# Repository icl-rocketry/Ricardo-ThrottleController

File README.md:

# C.H.A.D - Servo Control Board
2 servo channels controlled by PWM, with a buck converter set to output 6V or 8.4V @ 12A depending on configuration.

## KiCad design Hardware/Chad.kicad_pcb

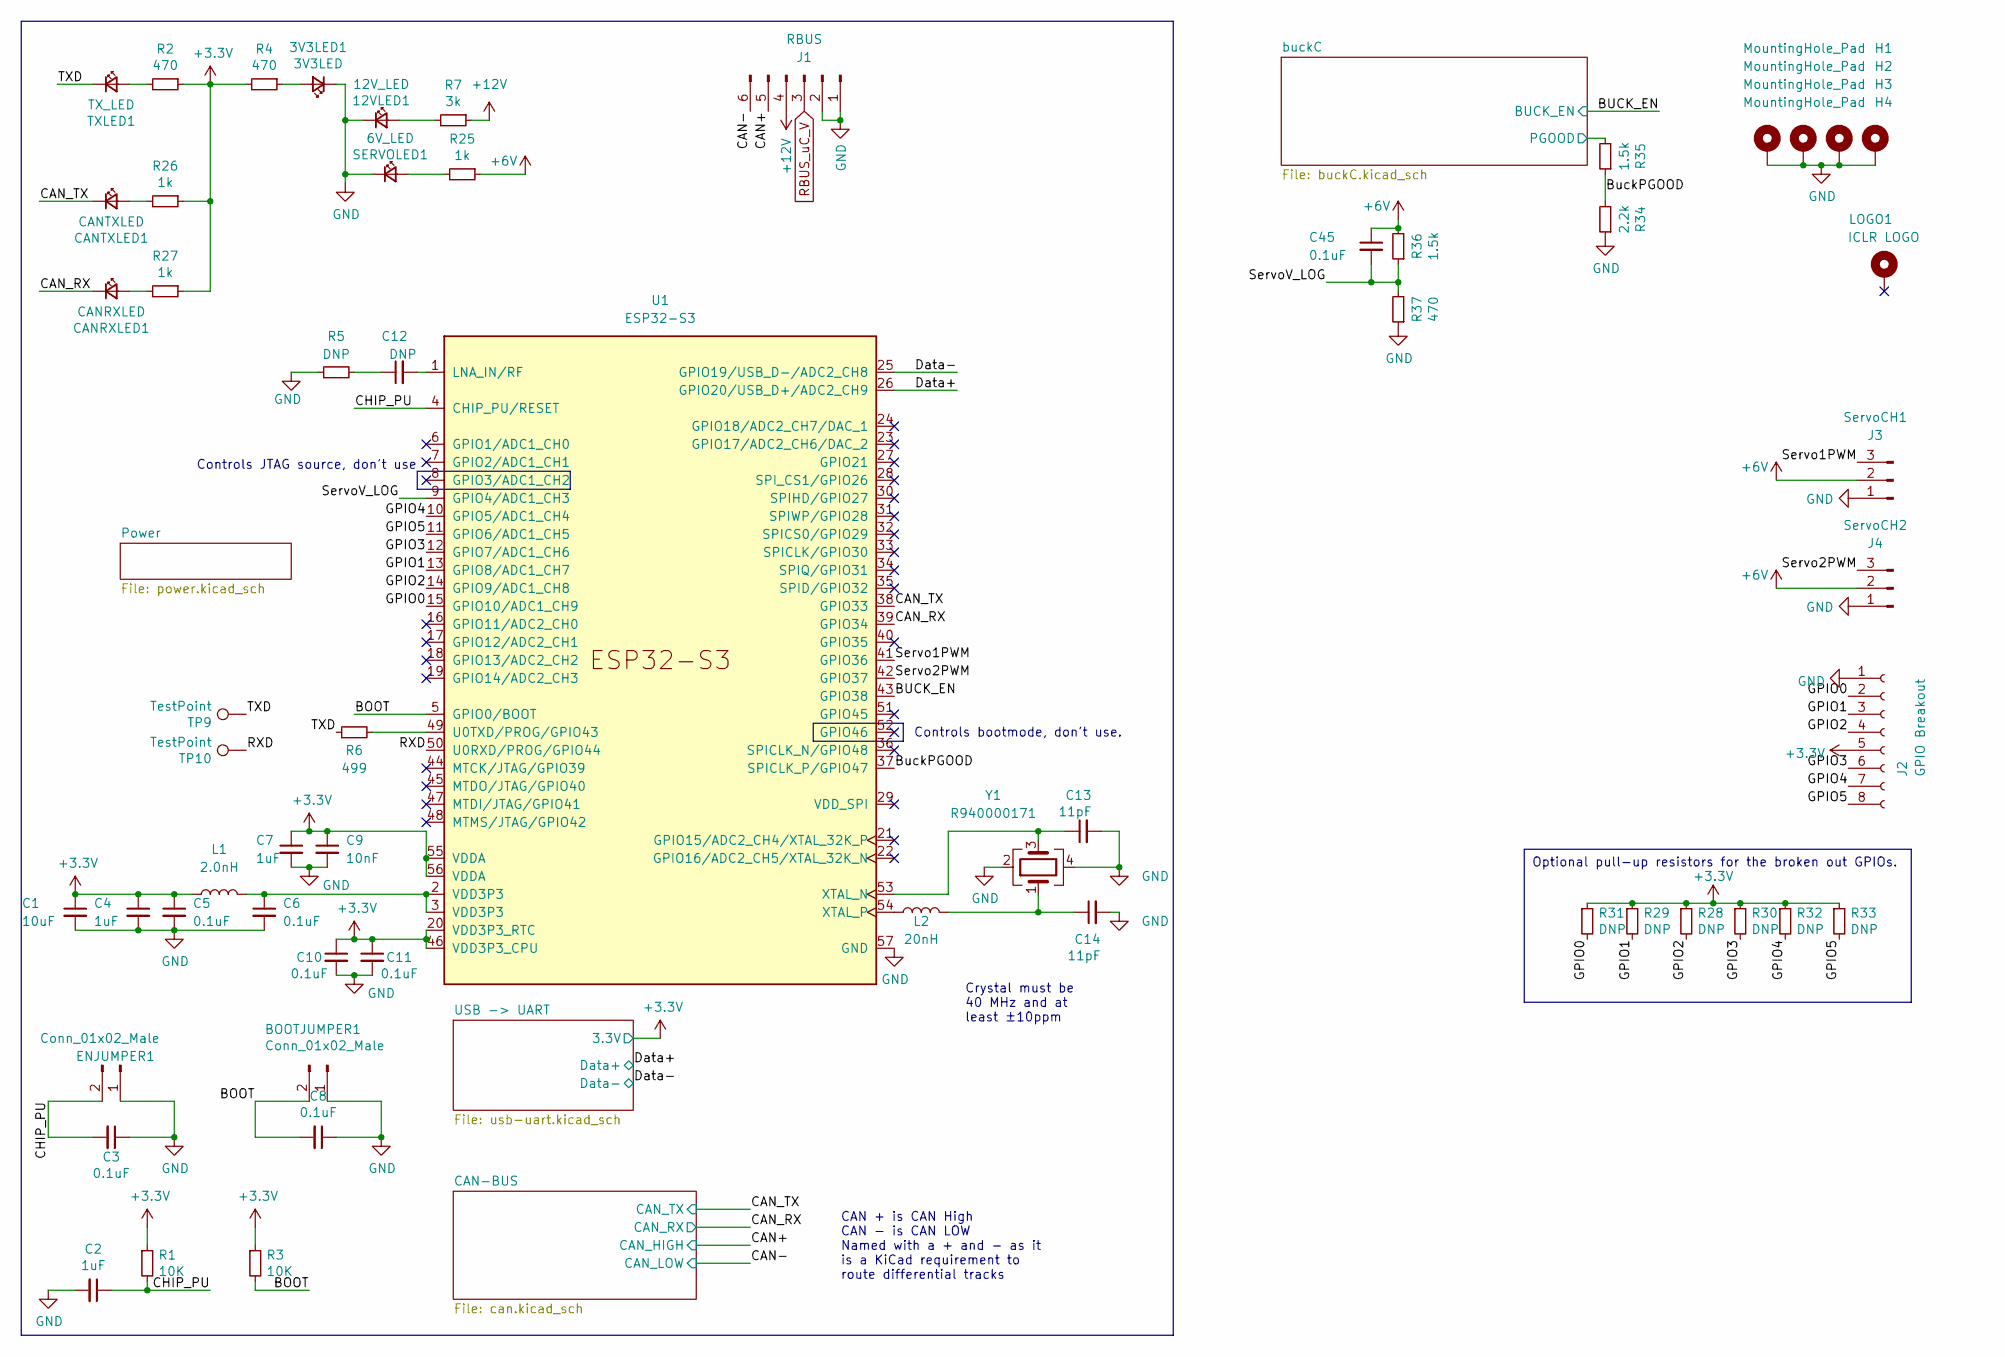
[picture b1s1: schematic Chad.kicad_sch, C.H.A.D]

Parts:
3V3LED1: 3V3LED; LED_0402_1005Metric
12VLED1: 12V_LED; LED_0402_1005Metric
BOOTJUMPER1: Conn_01x02_Male; PinHeader_1x02_P2.54mm_Vertical
C1: 10uF; C_0402_1005Metric
C2, C4, C7: 1uF; C_0402_1005Metric
C3, C5, C6, C8, C10, C11, C45: 0.1uF; C_0402_1005Metric
C9: 10nF; C_0402_1005Metric
C12: DNP; C_0402_1005Metric
C13, C14: 11pF; C_0402_1005Metric
CANRXLED1: CANRXLED; LED_0402_1005Metric
CANTXLED1: CANTXLED; LED_0402_1005Metric
ENJUMPER1: Conn_01x02_Male; PinHeader_1x02_P2.54mm_Vertical
H1, H2, H3, H4: MountingHole_Pad; MountingHole_3.2mm_M3_DIN965_Pad
J1: RBUS; Molex_Mini-Fit_Jr_5569-06A2_2x03_P4.20mm_Horizontal
J2: GPIO Breakout; PinSocket_2x04_P2.54mm_Vertical
J3: ServoCH1; Molex_Nano-Fit_105313-xx03_1x03_P2.50mm_Horizontal
J4: ServoCH2; Molex_Nano-Fit_105313-xx03_1x03_P2.50mm_Horizontal
L1: 2.0nH; L_0402_1005Metric
L2: 20nH; L_0402_1005Metric
LOGO1: ICLR LOGO; iclr_logo_estd2018_10mm
R1, R3: 10K; R_0402_1005Metric
R2, R4, R37: 470; R_0402_1005Metric
R5, R28, R29, R30, R31, R32, R33: DNP; R_0402_1005Metric
R6: 499; R_0402_1005Metric
R7: 3k; R_0402_1005Metric
R25, R26, R27: 1k; R_0402_1005Metric
R34: 2.2k; R_0402_1005Metric
R35, R36: 1.5k; R_0402_1005Metric
SERVOLED1: 6V_LED; LED_0402_1005Metric
TP9, TP10: TestPoint; TestPoint_Pad_D1.0mm
TXLED1: TX_LED; LED_0402_1005Metric
U1: ESP32-S3; QFN40P700X700X90-57N
Y1: R940000171; Crystal_SMD_2016-4Pin_2.0x1.6mm

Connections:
+3V3: C1.1, C4.1, C5.1, C7.1, C9.1, C10.1, C11.1, J2.5, L1.1, R1.1, R2.1, R3.1, R4.2, R26.1, R27.1, R28.1, R29.1, R30.1, R31.1, R32.1, R33.1, U1.20 (VDD3P3_RTC), U1.46 (VDD3P3_CPU), U1.55 (VDDA), U1.56 (VDDA); also elsewhere on the board
+6V: C45.1, J3.2, J4.2, R25.1, R36.2; also elsewhere on the board
+12V: J1.4, R7.1; also elsewhere on the board
/BOOT: BOOTJUMPER1.2, C8.2, R3.2, U1.5 (GPIO0/BOOT)
/BUCK_EN: U1.43 (GPIO38); also elsewhere on the board
/BuckPGOOD: R34.2, R35.1, U1.37 (SPICLK_P/GPIO47)
/CAN+: J1.5; also elsewhere on the board
/CAN-: J1.6; also elsewhere on the board
/CAN_RX: CANRXLED1.1 (K), U1.39 (GPIO34); also elsewhere on the board
/CAN_TX: CANTXLED1.1 (K), U1.38 (GPIO33); also elsewhere on the board
/CHIP_PU: C2.1, C3.2, ENJUMPER1.2, R1.2, U1.4 (CHIP_PU/RESET)
/Data+: U1.26 (GPIO20/USB_D+/ADC2_CH9); also elsewhere on the board
/Data-: U1.25 (GPIO19/USB_D-/ADC2_CH8); also elsewhere on the board
/GPIO0: J2.2, R31.2, U1.15 (GPIO10/ADC1_CH9)
/GPIO1: J2.3, R29.2, U1.13 (GPIO8/ADC1_CH7)
/GPIO2: J2.4, R28.2, U1.14 (GPIO9/ADC1_CH8)
/GPIO3: J2.6, R30.2, U1.12 (GPIO7/ADC1_CH6)
/GPIO4: J2.7, R32.2, U1.10 (GPIO5/ADC1_CH4)
/GPIO5: J2.8, R33.2, U1.11 (GPIO6/ADC1_CH5)
/RXD: TP10.1, U1.50 (U0RXD/PROG/GPIO44)
/Servo1PWM: J3.3, U1.41 (GPIO36)
/Servo2PWM: J4.3, U1.42 (GPIO37)
/ServoV_LOG: C45.2, R36.1, R37.2, U1.9 (GPIO4/ADC1_CH3)
/TXD: R6.1, TP9.1, TXLED1.1 (K)
/buckC/PGOOD: R35.2; also elsewhere on the board
GND: 3V3LED1.1 (K), 12VLED1.1 (K), BOOTJUMPER1.1, C1.2, C2.2, C3.1, C4.2, C5.2, C6.2, C7.2, C8.1, C9.2, C10.2, C11.2, C13.2, C14.2, ENJUMPER1.1, H1.1, H2.1, H3.1, H4.1, J1.1, J1.2, J2.1, J3.1, J4.1, R5.1, R34.1, R37.1, SERVOLED1.1 (K), U1.57 (GND), Y1.2, Y1.4; also elsewhere on the board
unnamed: 3V3LED1.2 (A), R4.1
unnamed: 12VLED1.2 (A), R7.2
unnamed: C6.1, L1.2, U1.2 (VDD3P3), U1.3 (VDD3P3)
unnamed: C12.1, R5.2
unnamed: C14.1, L2.2, Y1.1
unnamed: CANRXLED1.2 (A), R27.2
unnamed: CANTXLED1.2 (A), R26.2
unnamed: R25.2, SERVOLED1.2 (A)
unnamed: R2.2, TXLED1.2 (A)
unnamed: C12.2, U1.1 (LNA_IN/RF)
unnamed: R6.2, U1.49 (U0TXD/PROG/GPIO43)
unnamed: C13.1, U1.53 (XTAL_N), Y1.3
unnamed: L2.1, U1.54 (XTAL_P)
RBUS_uC_V: J1.3; also elsewhere on the board

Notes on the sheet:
Crystal must be 40 MHz and at least ±10ppm
Optional pull-up resistors for the broken out GPIOs.
Controls bootmode, don't use.
CAN + is CAN High CAN - is CAN LOW Named with a + and - as it is a KiCad requirement to route differential tracks
Controls JTAG source, don't use

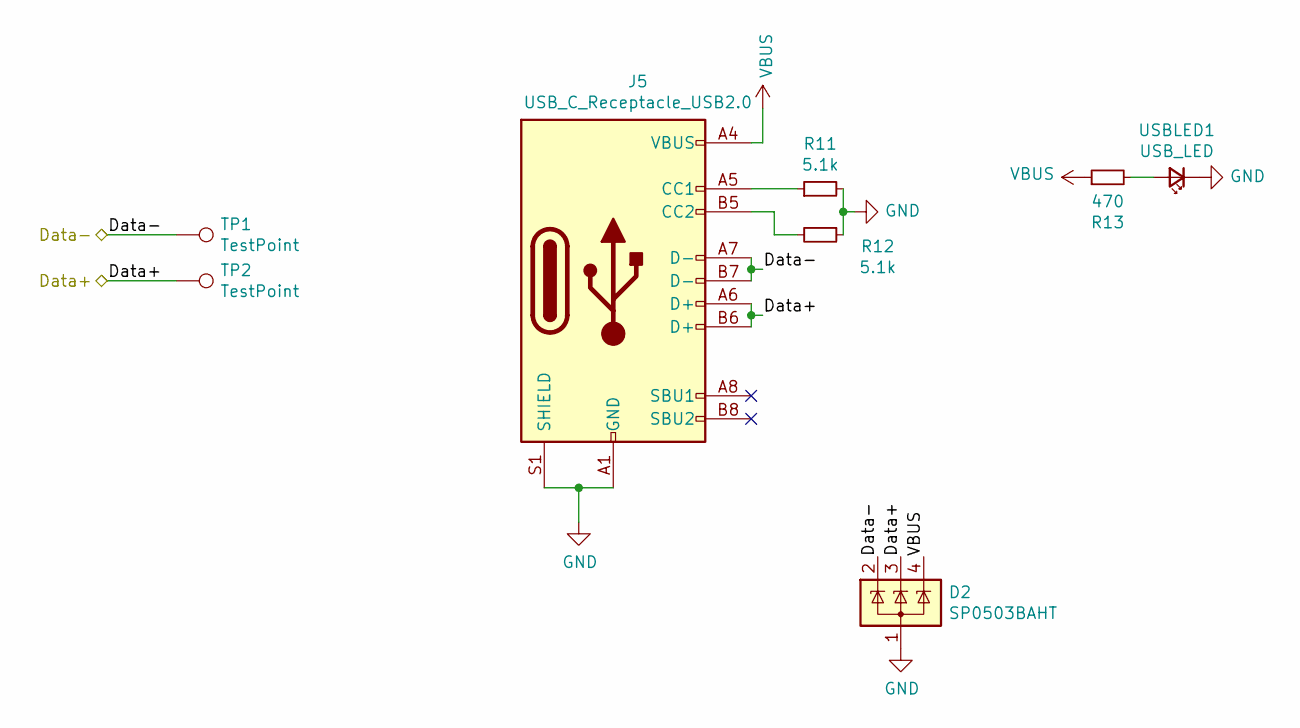
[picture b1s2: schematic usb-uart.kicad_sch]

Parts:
D2: SP0503BAHT; SOT-143
J5: USB_C_Receptacle_USB2.0; USB_C_Receptacle_Palconn_UTC16-G
R11, R12: 5.1k; R_0402_1005Metric
R13: 470; R_0402_1005Metric
TP1, TP2: TestPoint; TestPoint_Pad_D1.0mm
USBLED1: USB_LED; LED_0402_1005Metric

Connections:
/Data+: D2.3 (K), J5.A6 (D+), J5.B6 (D+), TP2.1; also elsewhere on the board
/Data-: D2.2 (K), J5.A7 (D-), J5.B7 (D-), TP1.1; also elsewhere on the board
GND: D2.1 (A), J5.A1 (GND), J5.A12 (GND), J5.B1 (GND), J5.B12 (GND), J5.S1 (SHIELD), R11.2, R12.1, USBLED1.1 (K); also elsewhere on the board
unnamed: J5.A5 (CC1), R11.1
unnamed: J5.B5 (CC2), R12.2
unnamed: R13.2, USBLED1.2 (A)
VBUS: D2.4 (K), J5.A4 (VBUS), J5.A9 (VBUS), J5.B4 (VBUS), J5.B9 (VBUS), R13.1; also elsewhere on the board

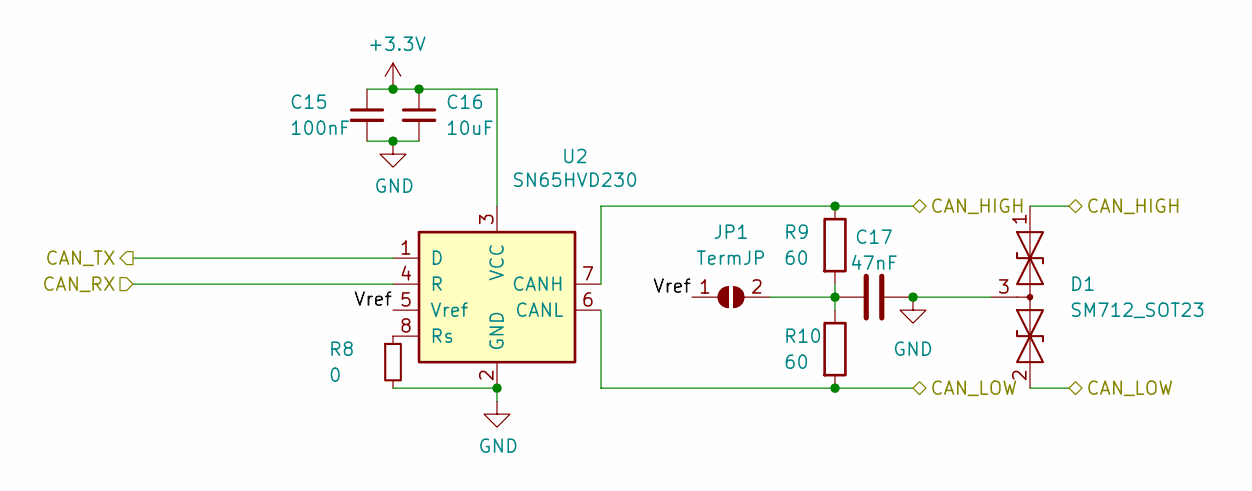
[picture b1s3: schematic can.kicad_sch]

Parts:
C15: 100nF; C_0402_1005Metric
C16: 10uF; C_0402_1005Metric
C17: 47nF; C_0402_1005Metric
D1: SM712_SOT23; SOT-23
JP1: TermJP; SmallerSolderJP
R8: 0; R_0603_1608Metric
R9, R10: 60; R_0603_1608Metric
U2: SN65HVD230; SOIC-8_3.9x4.9mm_P1.27mm

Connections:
+3V3: C15.1, C16.1, U2.3 (VCC); also elsewhere on the board
/CAN+: D1.1 (A1), R9.1, U2.7 (CANH); also elsewhere on the board
/CAN-: D1.2 (A2), R10.2, U2.6 (CANL); also elsewhere on the board
/CAN-BUS/Vref: JP1.1 (A), U2.5 (Vref)
/CAN_RX: U2.4 (R); also elsewhere on the board
/CAN_TX: U2.1 (D); also elsewhere on the board
GND: C15.2, C16.2, C17.2, D1.3 (common), R8.2, U2.2 (GND); also elsewhere on the board
unnamed: C17.1, JP1.2 (B), R9.2, R10.1
unnamed: R8.1, U2.8 (Rs)

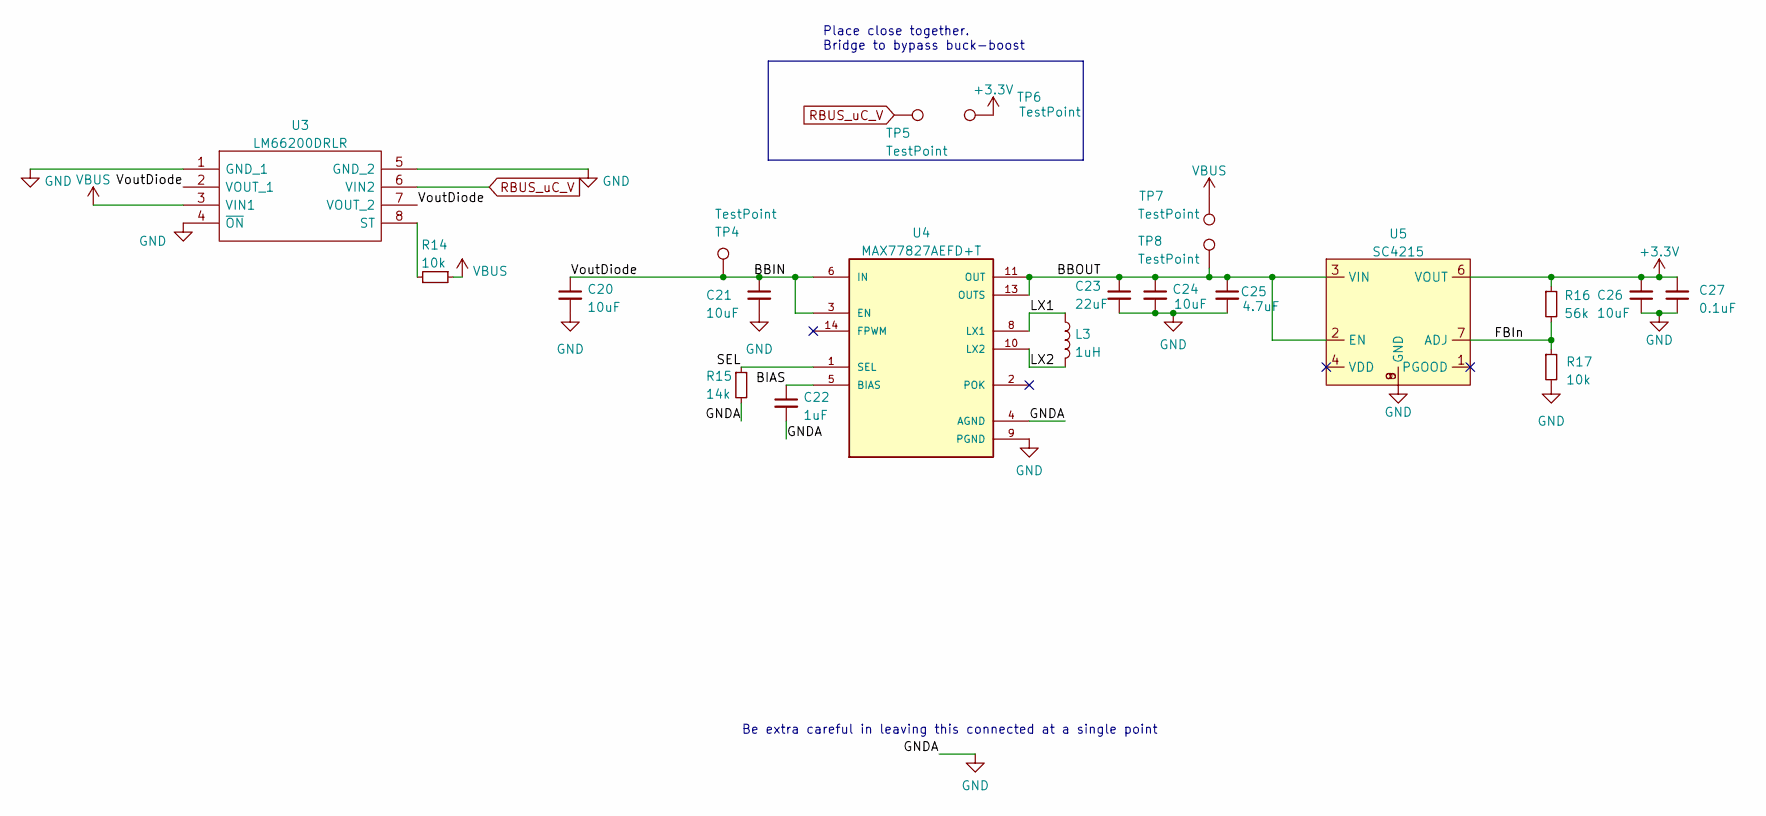
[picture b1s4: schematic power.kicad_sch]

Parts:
C20, C24, C26: 10uF; C_0402_1005Metric
C21: 10uF; C_0603_1608Metric
C22: 1uF; C_0402_1005Metric
C23: 22uF; C_0603_1608Metric
C25: 4.7uF; C_0402_1005Metric
C27: 0.1uF; C_0402_1005Metric
L3: 1uH; L_0805_2012Metric
R14, R17: 10k; R_0402_1005Metric
R15: 14k; R_0402_1005Metric
R16: 56k; R_0402_1005Metric
TP4, TP5, TP6, TP7, TP8: TestPoint; TestPoint_Pad_D1.5mm
U3: LM66200DRLR; SOTFL50P160X60-8N; Manufacturer_Part_Number LM66200DRLR; Mouser Part Number 595-LM66200DRLR
U4: MAX77827AEFD+T; CONV_MAX77827AEFD+T; PARTREV B
U5: SC4215; SOIC127P599X175-9N

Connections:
+3V3: C26.2, C27.2, R16.1, TP6.1, U5.6 (VOUT); also elsewhere on the board
/Power/BBIN: C20.1, C21.1, TP4.1, U3.2 (VOUT_1), U3.7 (VOUT_2), U4.3 (EN), U4.6 (IN)
/Power/BBOUT: C23.1, C24.1, C25.1, TP8.1, U4.11 (OUT), U4.13 (OUTS), U5.2 (EN), U5.3 (VIN)
/Power/BIAS: C22.1, U4.5 (BIAS)
/Power/FBIn: R16.2, R17.1, U5.7 (ADJ)
/Power/LX1: L3.1, U4.8 (LX1)
/Power/LX2: L3.2, U4.10 (LX2)
/Power/SEL: R15.1, U4.1 (SEL)
GND: C20.2, C21.2, C22.2, C23.2, C24.2, C25.2, C26.1, C27.1, R15.2, R17.2, U3.1 (GND_1), U3.4 (~ON), U3.5 (GND_2), U4.4 (AGND), U4.9 (PGND), U5.8 (GND), U5.9 (GND); also elsewhere on the board
unnamed: R14.2, U3.8 (ST)
RBUS_uC_V: TP5.1, U3.6 (VIN2); also elsewhere on the board
VBUS: R14.1, TP7.1, U3.3 (VIN1); also elsewhere on the board

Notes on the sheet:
Place close together. Bridge to bypass buck-boost
Be extra careful in leaving this connected at a single point

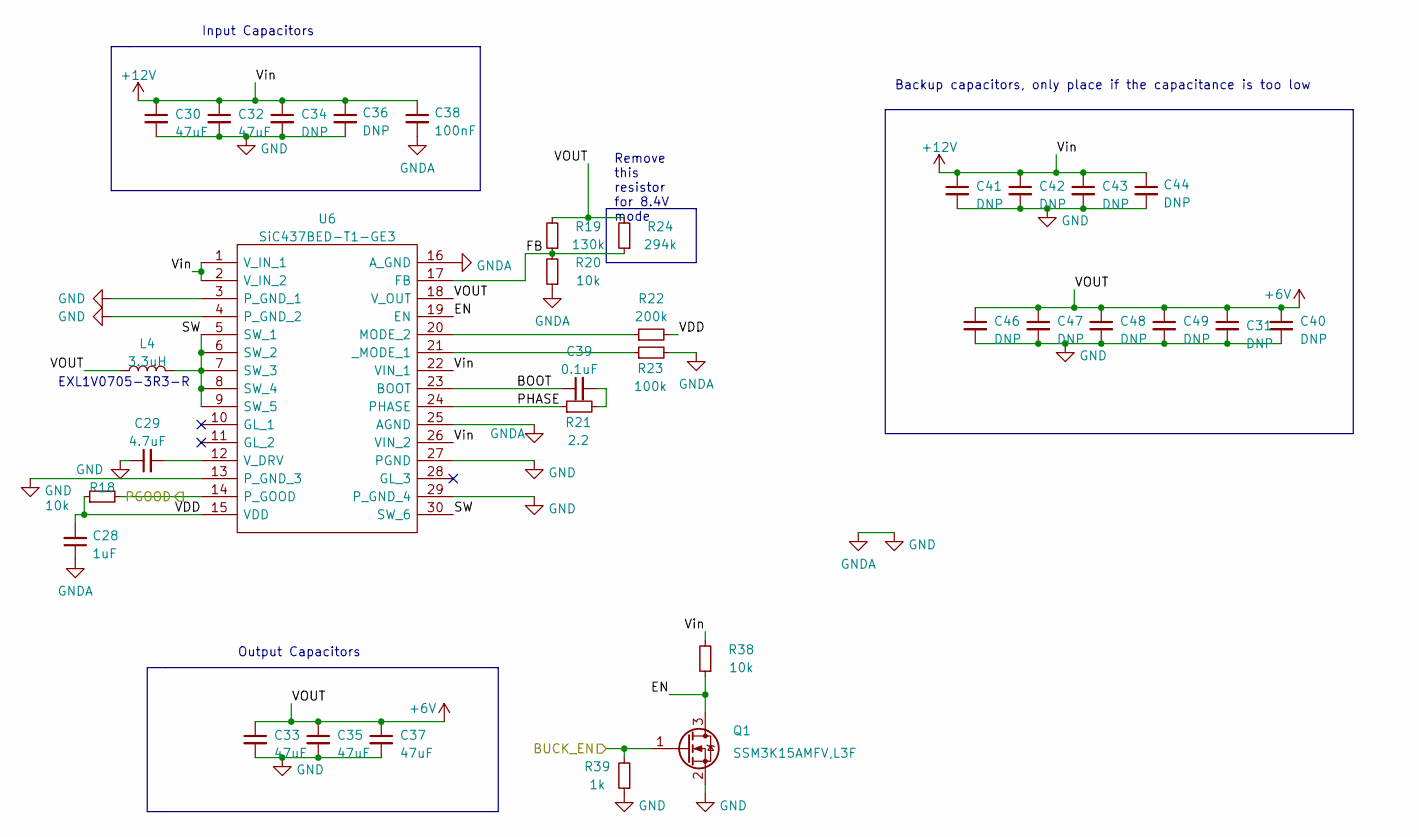
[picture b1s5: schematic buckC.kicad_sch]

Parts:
C28: 1uF; C_0402_1005Metric
C29: 4.7uF; C_0402_1005Metric
C30, C32, C33, C35, C37: 47uF; C_1206_3216Metric
C31, C34, C36, C40, C41, C42, C43, C44, C47, C49: DNP; C_1206_3216Metric
C38: 100nF; C_0402_1005Metric
C39: 0.1uF; C_0402_1005Metric
C46, C48: DNP; C_0805_2012Metric
L4: 3.3uH; EXL1V07053R3R
Q1: SSM3K15AMFV,L3F; SOT-723
R18, R20, R38: 10k; R_0402_1005Metric
R19: 130k; R_0402_1005Metric
R21: 2.2; R_0402_1005Metric
R22: 200k; R_0402_1005Metric
R23: 100k; R_0402_1005Metric
R24: 294k; R_0402_1005Metric
R39: 1k; R_0402_1005Metric
U6: SiC437BED-T1-GE3; SiC437BEDT1GE3; Manufacturer_Part_Number SiC437BED-T1-GE3; Mouser Part Number 78-SIC437BED-T1-GE3

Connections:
+6V: C31.1, C33.1, C35.1, C37.1, C40.1, C46.1, C47.1, C48.1, C49.1, L4.1, R19.2, R24.2, U6.18 (V_OUT); also elsewhere on the board
+12V: C30.1, C32.1, C34.1, C36.1, C38.1, C41.1, C42.1, C43.1, C44.1, R38.2, U6.1 (V_IN_1), U6.2 (V_IN_2), U6.22 (VIN_1), U6.26 (VIN_2); also elsewhere on the board
/BUCK_EN: Q1.1 (G), R39.2; also elsewhere on the board
/buckC/BOOT: C39.1, U6.23 (BOOT)
/buckC/EN: Q1.3 (D), R38.1, U6.19 (EN)
/buckC/FB: R19.1, R20.2, R24.1, U6.17 (FB)
/buckC/PGOOD: R18.2, U6.14 (P_GOOD); also elsewhere on the board
/buckC/PHASE: R21.1, U6.24 (PHASE)
/buckC/SW: L4.2, U6.5 (SW_1), U6.6 (SW_2), U6.7 (SW_3), U6.8 (SW_4), U6.9 (SW_5), U6.30 (SW_6)
/buckC/VDD: C28.2, R18.1, R22.2, U6.15 (VDD)
GND: C28.1, C29.1, C30.2, C31.2, C32.2, C33.2, C34.2, C35.2, C36.2, C37.2, C38.2, C40.2, C41.2, C42.2, C43.2, C44.2, C46.2, C47.2, C48.2, C49.2, Q1.2 (S), R20.1, R23.2, R39.1, U6.3 (P_GND_1), U6.4 (P_GND_2), U6.13 (P_GND_3), U6.16 (A_GND), U6.25 (AGND), U6.27 (PGND), U6.29 (P_GND_4); also elsewhere on the board
unnamed: C39.2, R21.2
unnamed: R22.1, U6.20 (MODE_2)
unnamed: C29.2, U6.12 (V_DRV)
unnamed: R23.1, U6.21 (_MODE_1)

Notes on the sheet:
Remove this resistor for 8.4V mode
Backup capacitors, only place if the capacitance is too low
EXL1V0705-3R3-R
Input Capacitors
Output Capacitors

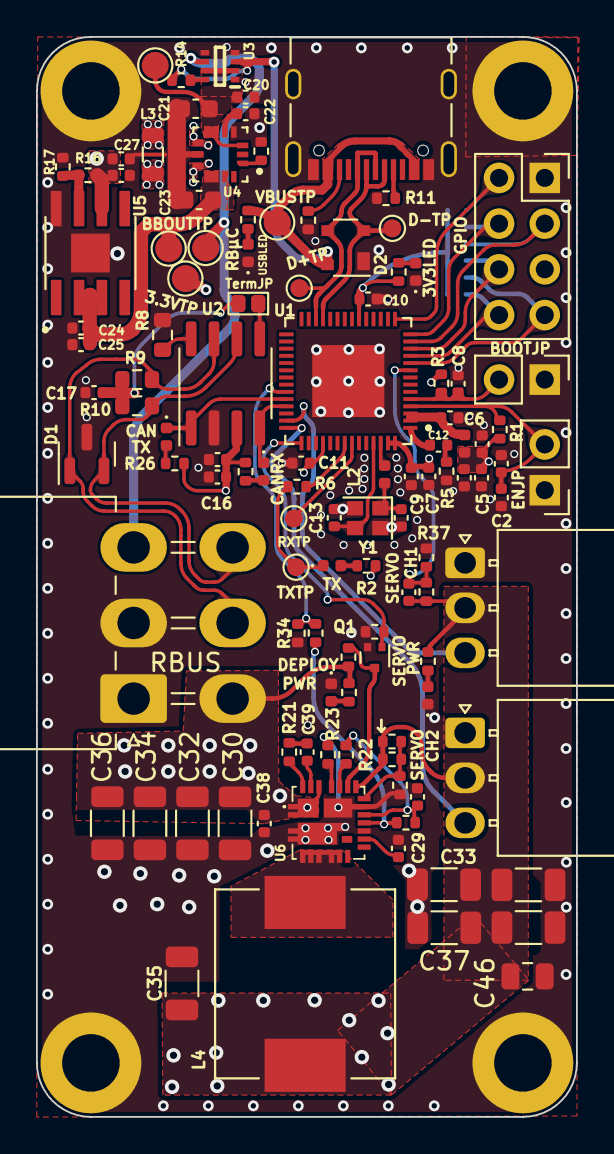
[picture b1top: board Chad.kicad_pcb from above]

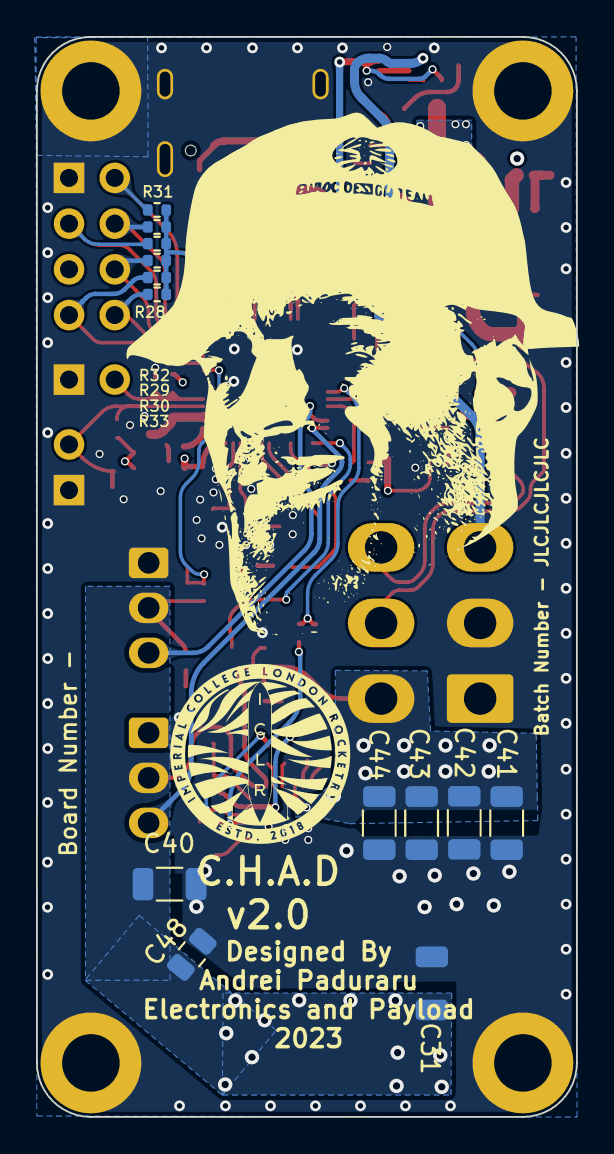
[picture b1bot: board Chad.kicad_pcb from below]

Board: 4 copper layers, 30.0 x 60.0 mm, 129 parts (14 on the bottom side), 65 nets.

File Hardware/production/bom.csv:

Designator,Footprint,Quantity,Value,LCSC Part #
12VLED1,0402,1,12V_LED,
3V3LED1,0402,1,3V3LED,
"BOOTJUMPER1, ENJUMPER1",PinHeader_1x02_P2.54mm_Vertical,2,Conn_01x02_Male,
"C1, C16, C20, C24, C26",0402,5,10uF,
"C10, C11, C27, C3, C39, C45, C5, C6, C8",0402,9,0.1uF,
C12,0402,1,4.2pF,
"C13, C14",0402,2,C,
"C15, C38",0402,2,100nF,
C17,0402,1,47nF,
"C2, C22, C28, C4, C7",0402,5,1uF,
C21,0603,1,10uF,
C23,0603,1,22uF,
"C25, C29",0402,2,4.7uF,
"C30, C32, C33, C35, C37",1206,5,47uF,
"C31, C34, C36, C40, C41, C42, C43, C44, C47, C49",1206,10,DNP,
"C46, C48",0805,2,DNP,
C9,0402,1,10nF,
CANRXLED1,0402,1,CANRXLED,
CANTXLED1,0402,1,CANTXLED,
D1,SOT-23,1,SM712_SOT23,
D2,SOT-143,1,SP0503BAHT,
"H1, H2, H3, H4",MountingHole_3.2mm_M3_DIN965_Pad,4,MountingHole_Pad,
J1,Molex_Mini-Fit_Jr_5569-06A2_2x03_P4.20mm_Horizontal,1,RBUS,
J2,PinSocket_2x04_P2.54mm_Vertical,1,GPIO Breakout,
J3,Molex_Nano-Fit_105313-xx03_1x03_P2.50mm_Horizontal,1,ServoCH1,
J4,Molex_Nano-Fit_105313-xx03_1x03_P2.50mm_Horizontal,1,ServoCH2,
J5,USB_C_Receptacle_Palconn_UTC16-G,1,USB_C_Receptacle_USB2.0,
JP1,SmallerSolderJP,1,TermJP,
L1,0402,1,2.0nH,
L2,0402,1,20nH,
L3,0805,1,1uH,
L4,IND_SPM10065VT-3R3M-D,1,3.3uH,
LOGO1,iclr_logo_estd2018_10mm,1,ICLR LOGO,
Q1,SOT-723,1,"SSM3K15AMFV,L3F",
"R1, R14, R17, R18, R20, R3, R38",0402,7,10K,
"R10, R9",0603,2,60,
"R11, R12",0402,2,5.1k,
"R13, R2, R37, R4",0402,4,470,
R15,0402,1,14k,
R16,0402,1,56k,
R19,0402,1,130k,
R21,0402,1,2.2,
R22,0402,1,200k,
R23,0402,1,100k,
R24,0402,1,294k,
"R25, R26, R27, R39",0402,4,1k,
"R28, R29, R30, R31, R32, R33",0402,6,DNP,
R34,0402,1,2.2k,
"R35, R36",0402,2,1.5k,
R5,0402,1,47.5,
R6,0402,1,499,
R7,0402,1,3k,
R8,0603,1,0,
SERVOLED1,0402,1,6V_LED,
"TP1, TP10, TP2, TP9",TestPoint_Pad_D1.0mm,4,TestPoint,
"TP4, TP5, TP6, TP7, TP8",TestPoint_Pad_D1.5mm,5,TestPoint,
TXLED1,0402,1,TX_LED,
U1,QFN40P700X700X90-57N,1,ESP32-S3,
U2,SOIC-8_3.9x4.9mm_P1.27mm,1,SN65HVD230,
U3,SOTFL50P160X60-8N,1,LM66200DRLR,
U4,CONV_MAX77827AEFD+T,1,MAX77827AEFD+T,
U5,SOIC127P599X175-9N,1,SC4215,
U6,SiC437BEDT1GE3,1,SiC437BED-T1-GE3,
USBLED1,0402,1,USB_LED,
Y1,Crystal_SMD_2016-4Pin_2.0x1.6mm,1,40MHz±10ppm,

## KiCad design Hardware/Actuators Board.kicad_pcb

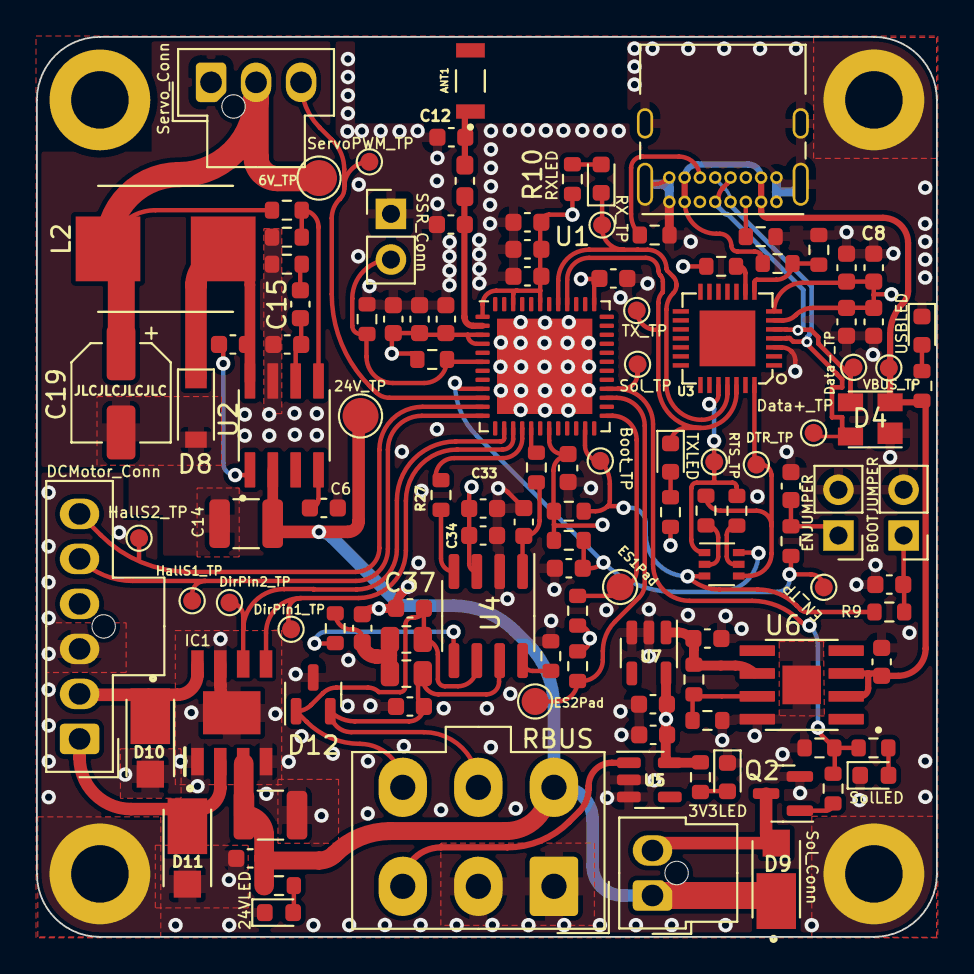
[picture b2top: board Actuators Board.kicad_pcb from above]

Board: 4 copper layers, 50.0 x 50.0 mm, 125 parts (0 on the bottom side), 60 nets.

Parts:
3V3LED1: 3V3LED; LED_0603_1608Metric
24VLED1: 24V_LED; LED_0603_1608Metric
ANT1: AMCA31-2R450G-S1F-T3; ANT_AMCA31-2R450G-S1F-T3
BOOTJUMPER1: Conn_01x02_Male; PinHeader_1x02_P2.54mm_Vertical
C1, C2, C3, C4, C9, C10, C16, C17, C29, C30, C31, C35: 0.1uF; C_0603_1608Metric
C5, C28: 1uF; C_0603_1608Metric
C6: 10 nF; C_0603_1608Metric
C7, C14: 10uF; C_1210_3225Metric
C8: 1.0uF; C_0603_1608Metric
C11: 33pF; C_0603_1608Metric
C12, C26: 100pF; C_0603_1608Metric
C13, C15: 130pF; C_0603_1608Metric
C18, C22, C23: 4.7uF; C_0603_1608Metric
C19: 100uF; CP_Elec_5x5.9
C20, C25, C27, C34: 10uF; C_0603_1608Metric
C32: 160pF; C_0603_1608Metric
C33: 100nF; C_0603_1608Metric
C36: 220pF; C_0603_1608Metric
C37: 220 pF; C_0603_1608Metric
D4: SP0503BAHT; SOT-143
D8: MBR260HWTR; D_SOD-123
D9, D10, D11: V8PAM10S; DIO_V3PAN50-M3_I
D12: SM712_SOT23; SOT-23
ENJUMPER1: Conn_01x02_Male; PinHeader_1x02_P2.54mm_Vertical
H1, H2, H3, H4: MountingHole_Pad; MountingHole_3.2mm_M3_DIN965_Pad
IC1: BD62120AEFJ-E2; SOIC127P600X100-9N
J1: Conn_01x05_Male; Molex_Mini-Fit_Jr_5566-06A_2x03_P4.20mm_Vertical
J2: Solenoid(Sol); Molex_Nano-Fit_105309-xx02_1x02_P2.50mm_Vertical
J3: USB_C_Receptacle_USB2.0; USB_C_Receptacle_GCT_USB4085
J4: Conn_01x03_Male; Molex_Nano-Fit_105309-xx03_1x03_P2.50mm_Vertical
J5: Conn_01x06_Male; Molex_Nano-Fit_105309-xx06_1x06_P2.50mm_Vertical
J6: Conn_01x02_Male; PinHeader_1x02_P2.54mm_Vertical
J7: Endstop Switch 1; TestPoint_Pad_D1.5mm
J8: Endstop Switch 2; TestPoint_Pad_D1.5mm
L1: LQG15WZ1N8B02D; L_0603_1608Metric_Pad1.05x0.95mm_HandSolder
L2: 33uH; IND_ETQP5M330YFM
Q1: MMDT2222A; SOT-363_SC-70-6
Q2: SI2366DS; SOT-23
R1, R2, R7, R8, R22: 10K; R_0603_1608Metric
R3: 24k; R_0603_1608Metric
R4: 3.5k; R_0603_1608Metric
R5, R9, R10, R11, R13, R14, R18: 470; R_0603_1608Metric
R6: 47k; R_0603_1608Metric
R12, R25, R28, R31, R32, R34, R35: 10k; R_0603_1608Metric
R15, R16: 5.1k; R_0603_1608Metric
R17: 4.7k; R_0603_1608Metric
R20: 54.9K; R_0603_1608Metric
R21: 110; R_0603_1608Metric
R23: 1.54K; R_0603_1608Metric
R24: 56k; R_0603_1608Metric
R26, R27: 90; R_0603_1608Metric
R29, R30: 60; R_0805_2012Metric
R33: 0; R_0603_1608Metric
RXLED1: RX_LED; LED_0603_1608Metric
SolLED1: Solenoid LED; LED_0603_1608Metric
TP1, TP2, TP3, TP4, TP5, TP9, TP10, TP11, TP12, TP13, TP16, TP17, TP18, TP19, TP24: TestPoint; TestPoint_Pad_D1.0mm
TP14, TP15: TestPoint; TestPoint_Pad_D2.0mm
TXLED1: TX_LED; LED_0603_1608Metric
U1: ESP32-PICO-D4; QFN-48-1EP_7x7mm_P0.5mm_EP5.3x5.3mm
U2: TPS54233D; SOIC127P599X175-8N
U3: CP2102-GMR-QFN28; QFN28G_0.5-5X5MM
U4: SN65HVD230; SOIC-8_3.9x4.9mm_P1.27mm
U5, U7: LTC4411; SOT-23-5
U6: RT9025-25GSP; SOIC127P599X175-9N
USBLED1: USB_LED; LED_0603_1608Metric

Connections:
+3V3: C4.1, C5.1, C8.2, C9.2, C10.2, C18.2, C22.1, C23.1, C26.1, C27.1, C28.1, C29.1, C30.1, C31.1, C33.1, C34.1, J5.4, R7.1, R8.1, R10.1, R11.1, R14.2, R17.1, R32.1, R34.1, R35.1, U1.1 (VDDA), U1.3 (VDDA3P3), U1.4 (VDDA3P3), U1.19 (VDD3P3_RTC), U1.37 (VDD3P3_CPU), U1.43 (VDDA), U1.46 (VDDA), U3.6 (VDD), U3.7 (REGIN), U4.3 (VCC), U5.5 (OUT), U7.5 (OUT)
+6V: C19.1, J4.2, L2.2, R22.1, TP15.1
+24V: C7.1, C14.1, C17.1, D9.C, IC1.3 (VCC), J1.4, J2.1, R4.1, TP14.1, U2.2 (VIN)
/BOOT: Q1.3 (C2), R8.2, R9.1, TP9.1, U1.23 (IO0)
/CAN-BUS/Vref: R33.1, U4.5 (Vref)
/CAN_HIGH: C36.2, D12.2 (A2), J1.5, R29.1, U4.7 (CANH)
/CAN_LOW: C37.2, D12.1 (A1), J1.6, R30.2, U4.6 (CANL)
/CAN_RX: R27.1, U1.16 (IO27)
/CAN_TX: R26.1, U1.17 (IO14)
/DTR: Q1.4 (E2), R1.2, TP4.1, U3.28 (DTR)
/EN: C2.1, Q1.6 (C1), R5.1, R7.2, TP5.1, U1.9 (EN)
/ES1GPIO: J7.1, R34.2, U1.25 (IO16)
/ES2GPIO: J8.1, R35.2, U1.27 (IO17)
/HBridgeDIR1: IC1.5 (IN1), TP24.1, U1.15 (IO26)
/HBridgeDIR2: IC1.6 (IN2), TP16.1, U1.14 (IO25)
/Hall1: J5.5, TP3.1, U1.12 (IO32)
/Hall2: J5.6, TP2.1, U1.11 (IO35)
/LNA_IN: C11.1, L1.1, U1.2 (LNA_IN)
/Motor+: D11.C, IC1.2 (OUT1), J5.1
/Motor-: D10.C, IC1.8 (OUT2), J5.2
/RTS: Q1.1 (E1), R2.2, TP1.1, U3.24 (RTS)
/RXD: RXLED1.1 (K), TP10.1, U1.41 (U0TXD/IO1), U3.25 (RXD)
/SSRGPIO: J6.2, R31.1, R32.2, U1.6 (SENSOR_CAPP)
/ServoPWM: J4.3, TP12.1, U1.10 (IO34)
/SolEN: R12.1, R13.2, R21.2, TP13.1, U1.28 (SD2/IO9)
/SolGND: D9.A, J2.2, Q2.3 (D)
/TXD: TP11.1, TXLED1.1 (K), U1.40 (U0RXD/IO3), U3.26 (TXD)
/USB -> UART/Data+: D4.4 (K), J3.A6 (D+), J3.B6 (D+), TP18.1, U3.4 (D+)
/USB -> UART/Data-: D4.3 (K), J3.A7 (D-), J3.B7 (D-), TP17.1, U3.5 (D-)
/VSENSE: R22.2, R23.1, U2.5 (VSENSE)
GND: 3V3LED1.1 (K), 24VLED1.1 (K), BOOTJUMPER1.2, C1.2, C2.2, C3.2, C4.2, C5.2, C6.2, C7.2, C8.1, C9.1, C10.1, C11.2, C12.2, C13.2, C14.2, C17.2, C18.1, C19.2, C20.1, C22.2, C23.2, C25.1, C26.2, C27.2, C28.2, C29.2, C30.2, C31.2, C32.1, C33.2, C34.2, C35.2, C36.1, C37.1, D4.1 (A), D8.2 (A), D10.A, D11.A, D12.3 (common), ENJUMPER1.2, H1.1, H2.1, H3.1, H4.1, IC1.1 (GND_1), IC1.4 (GND_2), IC1.7 (TEST), IC1.9 (GND), J1.1, J1.2, J3.A1 (GND), J3.A12 (GND), J3.B1 (GND), J3.B12 (GND), J3.S1 (SHIELD), J4.1, J5.3, J6.1, Q2.2 (S), R6.1, R12.2, R15.2, R16.1, R20.2, R23.2, R25.2, R28.2, R31.2, SolLED1.1 (K), U1.49 (GND), U2.7 (GND), U3.3 (GND), U4.2 (GND), U5.2 (GND), U5.3 (CTL), U6.8 (GND), U6.9 (GND), U7.2 (GND), U7.3 (CTL), USBLED1.1 (K)
unnamed: 3V3LED1.2 (A), R14.1
unnamed: 24VLED1.2 (A), R4.2
unnamed: ANT1.1, C12.1, L1.2
unnamed: BOOTJUMPER1.1, C3.1, R9.2
unnamed: C1.1, ENJUMPER1.1, R5.2
unnamed: C6.1, U2.4 (SS)
unnamed: C13.1, C15.1, U2.6 (COMP)
unnamed: C15.2, R20.1
unnamed: C16.1, U2.1 (BOOT)
unnamed: C16.2, D8.1 (K), L2.1, U2.8 (PH)
unnamed: C25.2, R24.1, U6.6 (VOUT), U7.1 (IN)
unnamed: C32.2, R26.2, U4.1 (D)
unnamed: C35.1, R29.2, R30.1, R33.2
unnamed: J1.3, U5.1 (IN)
unnamed: J3.A5 (CC1), R15.1
unnamed: J3.B5 (CC2), R16.2
unnamed: Q1.2 (B1), R1.1
unnamed: Q1.5 (B2), R2.1
unnamed: Q2.1 (G), R21.1
unnamed: R3.2, R6.2, U3.8 (VBUS)
unnamed: R10.2, RXLED1.2 (A)
unnamed: R11.2, TXLED1.2 (A)
unnamed: R13.1, SolLED1.2 (A)
unnamed: R17.2, U3.9 (~RST)
unnamed: R18.2, USBLED1.2 (A)
unnamed: R25.1, U6.7 (ADJ)
unnamed: R27.2, U4.4 (R)
unnamed: R28.1, U4.8 (Rs)
VBUS: C20.2, D4.2 (K), J3.A4 (VBUS), J3.A9 (VBUS), J3.B4 (VBUS), J3.B9 (VBUS), R3.1, R18.1, TP19.1, U6.2 (EN), U6.3 (VIN)
